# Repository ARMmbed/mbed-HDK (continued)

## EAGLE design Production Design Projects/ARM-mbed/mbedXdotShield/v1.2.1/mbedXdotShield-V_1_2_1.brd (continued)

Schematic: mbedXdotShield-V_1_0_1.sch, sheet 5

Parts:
BRD1: K64F/K22F-SHIELD; K64F/K22F
D1: BAT60A; SOD323
R14, R15, R16, R17, R18, R19, R20, R21, R22, R23, R24, R25, R26: 220R; 0402
R27: 0; 0402
SW3: JS202011JCQN

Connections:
GND: BRD1.6 (GND), BRD1.7 (GND), BRD1.29 (GND); also elsewhere on the board
GPIO2: R15.1; also elsewhere on the board
GPIO3: R16.1; also elsewhere on the board
I2C0_SCL: R26.2; also elsewhere on the board
I2C0_SDA: R25.2; also elsewhere on the board
unnamed: BRD1.9 (A0), R14.2
unnamed: BRD1.10 (A1), R15.2
unnamed: BRD1.11 (A2), R16.2
unnamed: BRD1.15 (D0/RX), R17.1
unnamed: BRD1.16 (D1/TX), R18.1
unnamed: BRD1.17 (D2), R19.1
unnamed: BRD1.5 (5V), D1.K
unnamed: BRD1.18 (D3), R20.1
unnamed: BRD1.25 (D10/SS), R21.1
unnamed: BRD1.26 (D11/MOSI), R22.1
unnamed: BRD1.27 (D12/MISO), R23.1
unnamed: BRD1.28 (D13/SCK), R24.1
unnamed: BRD1.31 (SDA), R25.1
unnamed: BRD1.32 (SCL), R26.1
unnamed: BRD1.2 (IOREF), BRD1.4 (3V3), R27.1
unnamed: R17.2, SW3.6
unnamed: R18.2, SW3.2
P5V-VIN: BRD1.8 (VIN); also elsewhere on the board
P5V_USB: D1.A; also elsewhere on the board
SPI_MISO: R23.2; also elsewhere on the board
SPI_MOSI: R22.2; also elsewhere on the board
SPI_NSS: R21.2; also elsewhere on the board
SPI_SCK: R24.2; also elsewhere on the board
TGT_NRESET: BRD1.3 (NRESET); also elsewhere on the board
UART1_CTS: R19.2; also elsewhere on the board
UART1_RTS: R20.2; also elsewhere on the board
UART1_RX: SW3.3, SW3.5; also elsewhere on the board
UART1_TX: SW3.1, SW3.7; also elsewhere on the board
WAKE: R14.1; also elsewhere on the board

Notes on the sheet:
Board Headers
UART Swap - DPDT Switch

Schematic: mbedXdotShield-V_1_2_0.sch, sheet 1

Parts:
ANT1: M620720
C1: 10uF; 0603
C2: 100nF; 0603
C3: 9.1pF; 0402
C4: 5.6pF; 0402
C5: 10pF; 0402
C6: 82pF; 0402
C7: 6.8pF; 0402
L1: 7.5nH; 0402
R1, R6: 0; 0402
U1: MTXDOT-EU1-A00-1; MTXDOT-EU1/NA1-A00-1

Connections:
ANT1: C3.1, C4.2, L1.1, R1.1, U1.P$37 (ANT1)
GND: C1.2, C2.2, C4.1, C5.1, C6.1, C7.1, U1.P$1 (GND(0)), U1.P$5 (GND(1)), U1.P$17 (GND(2)), U1.P$20 (GND(3)), U1.P$35 (GND(4)), U1.P$36 (GND(5)), U1.P$38 (GND(6)), U1.P$39 (GND(7)), U1.P$40 (GND(8)), U1.P$41 (GND(9)), U1.P$42 (GND(10)), U1.P$43 (GND(11)), U1.P$44 (GND(12)), U1.P$45 (GND(13)), U1.P$46 (GND(14)), U1.P$48 (GND(15)), U1.P$49 (GND(16)), U1.P$50 (GND(17)), U1.P$51 (GND(18)), U1.P$52 (GND(19)), U1.P$53 (GND(20)), U1.P$54 (GND(21)), U1.P$55 (GND(22)), U1.P$56 (GND(23)), U1.P$57 (GND(24)), U1.P$58 (GND(25)); also elsewhere on the board
GPIO0: U1.P$26 (GPIO0); also elsewhere on the board
GPIO1: U1.P$25 (GPIO1); also elsewhere on the board
GPIO2: U1.P$24 (GPIO2); also elsewhere on the board
GPIO3: U1.P$23 (GPIO3); also elsewhere on the board
I2C0_SCL: U1.P$27 (I2C0_SCL); also elsewhere on the board
I2C0_SDA: U1.P$28 (I2C0_SDA); also elsewhere on the board
unnamed: ANT1.P$3 (3), C7.2
unnamed: ANT1.P$1 (1), C3.2, C5.2, C6.2, L1.2, R1.2
RFU1: U1.P$2 (RFU1)
RFU2: R6.2, U1.P$6 (RFU2)
RFU3: U1.P$7 (RFU3)
RFU4: U1.P$8 (RFU4)
RFU5: U1.P$18 (RFU5)
RFU6: U1.P$19 (RFU6)
RFU7: U1.P$21 (RFU7)
RFU8: U1.P$22 (RFU8)
SPI_MISO: U1.P$12 (SPI_MISO); also elsewhere on the board
SPI_MOSI: U1.P$11 (SPI_MOSI); also elsewhere on the board
SPI_NSS: U1.P$9 (SPI_NSS); also elsewhere on the board
SPI_SCK: U1.P$10 (SPI_SCK); also elsewhere on the board
TGT_NRESET: U1.P$33 (NRESET); also elsewhere on the board
TGT_RX: U1.P$16 (UART0_RX); also elsewhere on the board
TGT_SWCLK: U1.P$29 (SWCLK); also elsewhere on the board
TGT_SWDIO: U1.P$30 (SWDIO); also elsewhere on the board
TGT_TX: U1.P$15 (UART0_TX); also elsewhere on the board
UART1_CTS: U1.P$32 (UART1_CTS); also elsewhere on the board
UART1_RTS: U1.P$31 (UART1_RTS); also elsewhere on the board
UART1_RX: U1.P$14 (UART1_RX); also elsewhere on the board
UART1_TX: U1.P$13 (UART1_TX); also elsewhere on the board
WAKE: U1.P$34 (WAKE); also elsewhere on the board

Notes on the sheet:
Target Microcontroller - Multitech xDOT
DNP

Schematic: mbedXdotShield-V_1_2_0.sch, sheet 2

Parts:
C8, C9, C16: 10uF; 0603
CON1: 47346-0001; USB-MICRO-B-H
CON2: S2B-PH-SM4-TB(LF)(SN)
D3, D4, D5: BAT60A; SOD323
R29: 0; 0805
U2: TLV73333PDBVT; SOT23-5

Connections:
GND: C8.2, C9.2, C16.2, CON1.GND, CON2.2 (-), U2.2 (GND); also elsewhere on the board
P5V-VIN: D4.A; also elsewhere on the board
P5V_USB: C16.1, CON1.VBUS, D3.A; also elsewhere on the board
USB_D+: CON1.D+; also elsewhere on the board
USB_D-: CON1.D-; also elsewhere on the board

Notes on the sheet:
3.3V Regulator
Micro USB Connector
4.5V Battery Connector

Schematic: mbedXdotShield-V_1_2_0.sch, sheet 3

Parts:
C10, C11: 100nF; 0402
C12, C13, C14, C15: 18pF; 0402
D6: BAT60J; SOD323
LED3: RED; CHIPLED_0603
LED4: BLUE; CHIPLED_0603
LED5: GREEN; CHIPLED_0603
Q1: 12MHz; 3.2X.2.5
R4, R7: 33R; 0402
R8, R12, R13: 1.5K; 0402
R9, R10: 10K; 0402
R11: 470R; 0402
RESET: SKRKAEE010
T1: BSS84; SOT23-3
U4: IF-LPC11U35; HVQFN33

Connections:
GND: C10.2, C11.2, C12.2, C13.2, C14.2, C15.2, RESET.P$1, U4.EXP (VSS); also elsewhere on the board
HID: R12.2, U4.12 (LED_HID)
IF_NRESET: C10.1, R9.2, U4.2 (IF_NRESET)
ISP: D6.K, RESET.P$2 (S), U4.1 (NRESET_FB_BL), U4.3 (NRESET_FB_ISP)
MSD: R11.2, U4.7 (LED_MSD)
unnamed: C13.1, R4.2, R8.2, U4.14 (USB_D+)
unnamed: C12.1, R7.2, U4.13 (USB_D-)
unnamed: T1.1 (G), U4.15 (USB_SCON)
unnamed: R8.1, T1.3 (D)
unnamed: R10.2, U4.9 (USB_VBUS)
unnamed: LED3.C, R11.1
unnamed: LED4.C, R12.1
unnamed: LED5.C, R13.1
unnamed: C15.1, Q1.P$3 (2), U4.5 (XTALOUT)
unnamed: C14.1, Q1.P$1 (1), U4.4 (XTALIN)
TGT_NRESET: D6.A, U4.8 (TGT_NRESET); also elsewhere on the board
TGT_RX: U4.32 (TGT_RX); also elsewhere on the board
TGT_SWCLK: U4.16 (TGT_SWCLK); also elsewhere on the board
TGT_SWDIO: U4.17 (TGT_SWDIO); also elsewhere on the board
TGT_TX: U4.31 (TGT_TX); also elsewhere on the board
UART: R13.2, U4.21 (LED_UART)
USB_D+: R4.1; also elsewhere on the board
USB_D-: R7.1; also elsewhere on the board

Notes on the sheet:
LCP11u35 DAPLINK Interface

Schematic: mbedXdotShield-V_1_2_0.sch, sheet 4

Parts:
C17: 100nF; 0603
LED1: SMD_LED0603; CHIPLED_0603
LED2: SMD_LED1206; CHIPLED_1206
R2, R5: 1.5K; 0402
R3: 220R; 0402
R28: 0; 0402
SW1: SKRKAEE010
U3: AT45DB321E-SHF-B; SO8

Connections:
GND: C17.1, LED1.C, LED2.C, SW1.P$2 (S), U3.7 (GND); also elsewhere on the board
GPIO0: R3.2; also elsewhere on the board
GPIO1: R5.1, SW1.P$1; also elsewhere on the board
unnamed: LED2.A, R3.1
unnamed: LED1.A, R2.1
unnamed: C17.2, R28.1, U3.6 (VCC)
SPI_MISO: U3.8 (SO); also elsewhere on the board
SPI_MOSI: U3.1 (SI); also elsewhere on the board
SPI_NSS: U3.4 (!CS); also elsewhere on the board
SPI_SCK: U3.2 (SCK); also elsewhere on the board

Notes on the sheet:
SW2
Power LED
User LED
SPI Flash Memory

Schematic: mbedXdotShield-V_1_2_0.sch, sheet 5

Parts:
BRD1: K64F/K22F-SHIELD; K64F/K22F
D1: BAT60A; SOD323
R14, R15, R16, R17, R18, R19, R20, R21, R22, R23, R24, R25, R26: 220R; 0402
R27: 0; 0402
SW3: JS202011JCQN

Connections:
GND: BRD1.6 (GND), BRD1.7 (GND), BRD1.29 (GND); also elsewhere on the board
GPIO2: R15.1; also elsewhere on the board
GPIO3: R16.1; also elsewhere on the board
I2C0_SCL: R26.2; also elsewhere on the board
I2C0_SDA: R25.2; also elsewhere on the board
unnamed: BRD1.9 (A0), R14.2
unnamed: BRD1.10 (A1), R15.2
unnamed: BRD1.11 (A2), R16.2
unnamed: BRD1.15 (D0/RX), R17.1
unnamed: BRD1.16 (D1/TX), R18.1
unnamed: BRD1.17 (D2), R19.1
unnamed: BRD1.5 (5V), D1.K
unnamed: BRD1.18 (D3), R20.1
unnamed: BRD1.25 (D10/SS), R21.1
unnamed: BRD1.26 (D11/MOSI), R22.1
unnamed: BRD1.27 (D12/MISO), R23.1
unnamed: BRD1.28 (D13/SCK), R24.1
unnamed: BRD1.31 (SDA), R25.1
unnamed: BRD1.32 (SCL), R26.1
unnamed: BRD1.2 (IOREF), BRD1.4 (3V3), R27.1
unnamed: R17.2, SW3.6
unnamed: R18.2, SW3.2
P5V-VIN: BRD1.8 (VIN); also elsewhere on the board
P5V_USB: D1.A; also elsewhere on the board
SPI_MISO: R23.2; also elsewhere on the board
SPI_MOSI: R22.2; also elsewhere on the board
SPI_NSS: R21.2; also elsewhere on the board
SPI_SCK: R24.2; also elsewhere on the board
TGT_NRESET: BRD1.3 (NRESET); also elsewhere on the board
UART1_CTS: R19.2; also elsewhere on the board
UART1_RTS: R20.2; also elsewhere on the board
UART1_RX: SW3.3, SW3.5; also elsewhere on the board
UART1_TX: SW3.1, SW3.7; also elsewhere on the board
WAKE: R14.1; also elsewhere on the board

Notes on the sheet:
Board Headers
UART Swap - DPDT Switch

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
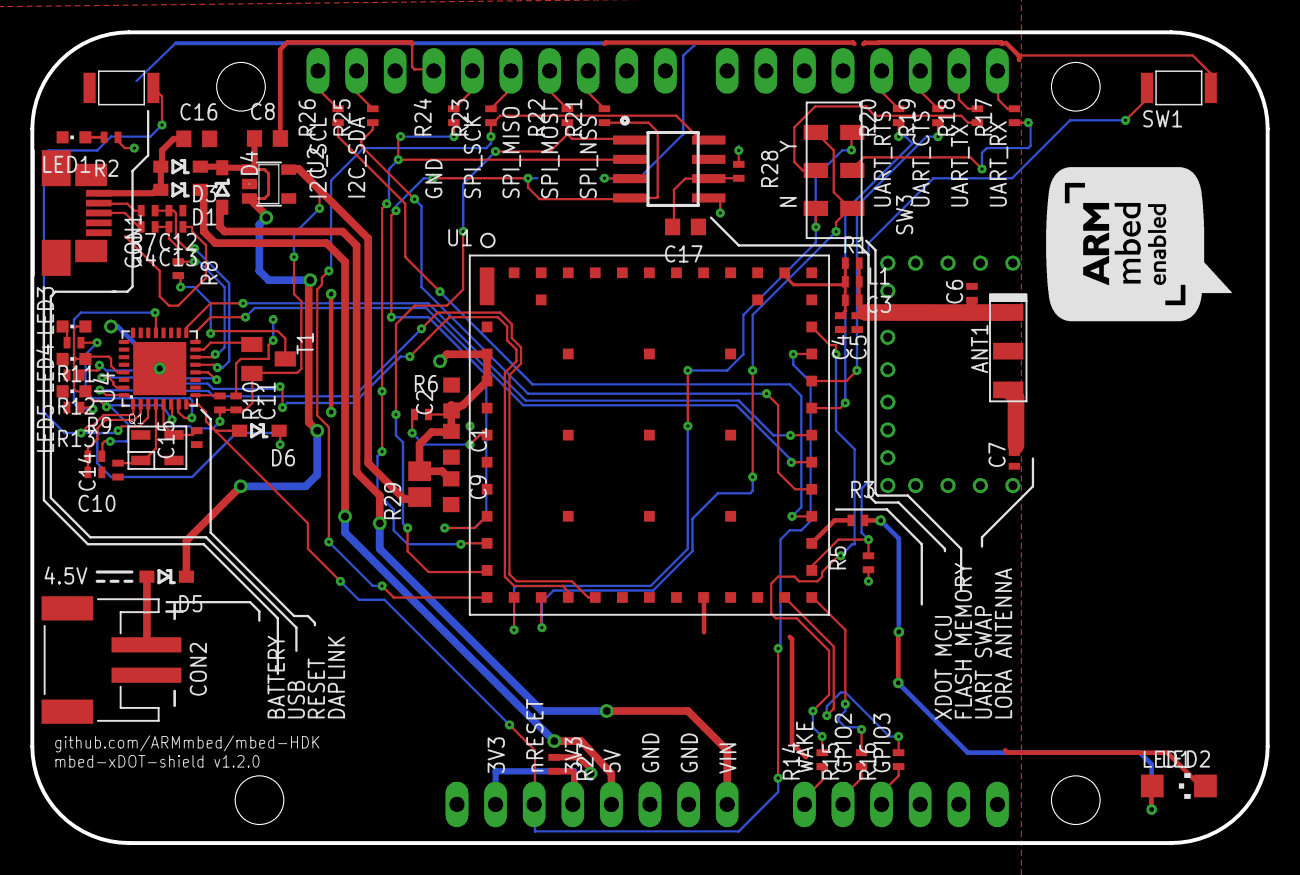
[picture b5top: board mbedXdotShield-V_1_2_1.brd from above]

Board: 2 copper layers, 81.3 x 53.3 mm, 70 parts (0 on the bottom side), 68 nets.

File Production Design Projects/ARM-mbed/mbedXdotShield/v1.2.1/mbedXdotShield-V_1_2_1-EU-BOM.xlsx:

Qty | Value | Device | Package | Parts | Description | MF | MFN | OC-DIGIKEY | OC-MOUSER | OC-NEWARK
1 |  | IF-LPC11U35 | HVQFN33 | U4 | MCU | NXP | LPC11U35FHI33/501, | 568-9586-ND | 771-LPC11U35FHI33501 | 24W5342
3 | 0 | RESISTOR0402 | 402 | R6, R27, R28 | Resistor | Yageo | RC0402JR-070RL | 311-0.0JRCT-ND | 603-RC0402JR-070RL | 603-RC0402JR-070RL
5 | 1.5K | RESISTOR0402 | 402 | R2, R5, R8, R12, R13 | Resistor | Panasonic | ERJ-2RKF1501X | P1.50KLCT-ND | 667-ERJ-2RKF1501X | 2302656
2 | 100nF | CAPACITOR0402 | 402 | C10, C11 | Capacitor | AVX | 0402YD104KAT2A | 478-1126-1-ND | 581-0402YD104K | 1327666
2 | 100nF | CAPACITOR0603 | 603 | C2, C17 | Capacitor | AVX | 0603YC104KAT2A | 478-1239-1-ND | 581-060316C104K | 1327679
2 | 10K | RESISTOR0402 | 402 | R9, R10 | Resistor | Vishay | CRCW040210K0JNED | 541-10KJCT-ND | 71-CRCW0402J-10K-E3 | 59M6696
4 | 10uF | CAPACITOR0603 | 603 | C1, C8, C9, C16 | Capacitor | Yageo | CC0603MRX5R5BB106 | 311-1448-1-ND | 603-CC603MRX5R5BB106 | 1458902
1 | 12MHz | Q_3.2X2.5 | 3.2X.2.5 | Q1 | XTAL | TXC | 7M-12.000MAAJ-T | 887-1121-1-ND | 717-7M-12.000MAAJ-T | 84R5706
4 | 18pF | CAPACITOR0402 | 402 | C12, C13, C14, C15 | Capacitor | Murata | GRM1555C1H180JA01D | 490-5858-6-ND |  | 14T3293
14 | 220R | RESISTOR0402 | 402 | R3, R14, R15, R16, R17, R18, R19, R20, R21, R22, R23, R24, R25, R26 | Resistor | Vishay | CRCW0402220RJNED | 541-220JCT-ND | 71-CRCW0402J-220-E3 | 1514687
2 | 33R | RESISTOR0402 | 402 | R4, R7 | Resistor | Vishay | CRCW040233R0JNED | 541-33JCT-ND | 71-CRCW0402J-33-E3 | 72M6782
1 | 470R | RESISTOR0402 | 402 | R11 | Resistor | Vishay | CRCW0402470RJNED | 541-470JCT-ND | 71-CRCW0402J-470-E3 | 59M6737
1 | 47346-0001 | 47346-0001 | USB-MICRO-B-H | CON1 | USB Receptacle Horizontal Micro Type B | MOLEX | 47346-0001 |  | 538-47346-0001 | 1568026
1 | 5.6pF | CAPACITOR0402 | 402 | C4 | Capacitor | AVX | 04025U5R6BAT2A | 478-10162-1-ND | 581-04025U5R6BAT2A | 1327642RL
1 | 6.8pF | CAPACITOR0402 | 402 | C7 | Capacitor | Murata | GRM1555C1H6R8BA01D | 490-6252-1-ND | 81-GRM1555C1H6R8BA1D | 2611902
1 | 82pF | CAPACITOR0402 | 402 | C6 | Capacitor | Murata | GRM1555C1H820JA01D | 490-5879-1-ND | 81-GRM1555C1H820JA1D | 2470460
1 | 9.1pF | CAPACITOR0402 | 402 | C3 | Capacitor | Murata | GJM1555C1H9R1CB01D | 490-3112-1-ND | 81-GJM1555C1H9R1CB01 | 41M1583
1 | 0 | RESISTOR0805 | 805 | R29 | Resistor | Yageo | RC0805JR-070RL | 311-0.0ARCT-ND | 603-RC0805JR-070RL | 1799478
1 | AT45DB321E-SHF-B | AT45DB321E-SHF-B | SO8 | U3 | Serial Flash 32 Mb 85 Mhz | Adesto Technologies | AT45DB321E-SHF-B | 1265-1072-5-ND | 988-AT45DB321E-SHF-B | 2414318
4 | BAT60A | BAT60A | SOD323 | D1, D3, D4, D5 | SCHOTTKY DIODE | Infineon | BAT60AE6327HTSA1 | BAT60AE6327HTSA1CT-ND | 726-BAT60AE6327 | 85X4127
1 | BAT60J | BAT60J | SOD323 | D6 | SCHOTTKY DIODE | STMicroelectronics | BAT60JFILM | 497-3707-6-ND | 511-BAT60JFILM | 89K1218
1 | BLUE | SMD_LED0603 | CHIPLED_0603 | LED4 | LED SMD, Colour Blue | Wurth Electronics Inc | 150060BS75000 | 732-4966-1-ND | 710-150060BS75000 | 2322069
1 | BSS84 | BSS84 | SOT23-3 | T1 | MOSFET P-CHANNEL | Fairchild Semiconductor | BSS84 | BSS84CT-ND | 512-BSS84 | 58K8770
1 | GREEN | SMD_LED0603 | CHIPLED_0603 | LED5 | LED SMD, Colour Green | Wurth Electronics Inc | 150060GS75000 | 732-4971-1-ND | 710-150060GS75000 | 2322070
1 | K64F/K22F-SHIELD | K64F/K22F-SHIELD | K64F/K22F | BRD1 | Shield for K64F/K22F | SparkFun | 1568-1413-ND
1 | M620720 | M620720 | M620720 | ANT1 | Chip Antenna Ceramic ISM/M2M/IoT 868/915MHz | Ethertronics | M620720 | 939-1066-1-ND
1 | MTXDOT-EU1-A00-1 | MTXDOT-EU1-A00-1 | MTXDOT-EU1/NA1-A00-1 | U1 | Multitech xDOT LORA MODULE UFL/TRC 868MHz for Europe | Multi-Tech Systems Inc. | MTXDOT-EU1-A00-1 | 591-1292-ND
2 | RED | SMD_LED0603 | CHIPLED_0603 | LED1, LED3 | LED SMD, Colour Red | Wurth Electronics Inc | 150060RS75000 | 732-4978-1-ND | 710-150060RS75000 | 2322071
1 | S2B-PH-SM4-TB(LF)(SN) | S2B-PH-SM4-TB(LF)(SN) | S2B-PH-SM4-TB(LF)(SN) | CON2 | 2 Position 2 mm JST PH Series Pitch Surface Mount Side Entry Shrouded Header | JST | S2B-PH-SM4-TB(LF)(SN) | 455-1749-1-ND |  | 38K8067
2 | SKRKAEE010 | SKRKAEE010 | SKRKAEE010 | RESET, SW2 | MOMENTARY SWITCH PUSH VERTICAL (SPST) | ALPS | SKRKAEE010 |  | 688-SKRKAE
1 | SMD_LED1206 | SMD_LED1206 | CHIPLED_1206 | LED2 | LED SMD, Colour Blue | Wurth Electronics Inc | 150120BS75000 | 732-4989-1-ND | 710-150120BS75000 | 2322084
1 | TLV73333PDBVT | TLV73333PDBVT | SOT23-5 | U2 | LDO Fixed Regulator 3.3v, 300mA | Texas Instruments | TLV73333PDBVT | 296-38492-1-ND | 595-TLV73333PDBVT | 2455145
1 | JS202011JCQN | JS202011JCQN | JS202011JCQN | SW3 | SLIDE TOGGLE SWITCH VERTICAL (DPDT) | C&K Components | JS202011JCQN | CKN10723CT-ND | 611-JS202011JCQN

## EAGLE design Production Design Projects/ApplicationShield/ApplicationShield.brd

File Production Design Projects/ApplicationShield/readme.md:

## Application Shield

The Application Shield includes an array of connectivity, sensors and display options to enable the maximum number of potential experiments with Arduino form factor mbed development boards.

## Whats included here?

* Eagle Schematic and Board files
* PDF Schematic and Board copies
* CAM Job GERBERS for manufacture (including pick/place and drill)
* BOM (Bill of Materials) In .csv or eBOM

## Hardware

The hardware design files can be found in this repo as part of the mbed HDK. The design features:

        1. 128x32 Graphics LCD
        2. 5 way joystick
        3. 2 x Potentiometers
        4. Speaker, PWM Conencted
        5. 3 Axis +/1 1.5g Accelerometer
        6. RGB LED, PWM connected
        7. Temperature sensor
        8. Socket for for Xbee (Zigbee) or RN-XV (Wifi)

## Software and more info

The software and more info can be found in the [mbed component page](https://developer.mbed.org/components/mbed-Application-Shield/). 

## How to get hardware

1. Buy pre-assembled board from   
  * [Cool Components](http://www.coolcomponents.co.uk/mbed-application-shield.html)
  * [Switch Science](http://international.switch-science.com/catalog/1810/)
  * [Farnell](http://uk.farnell.com/keil/mbed-016-1/application-shield-arduino-dev/dp/2468119)
2. Do it yourself, using supplied GERBERS and BOM/eBOM with fabrication house.

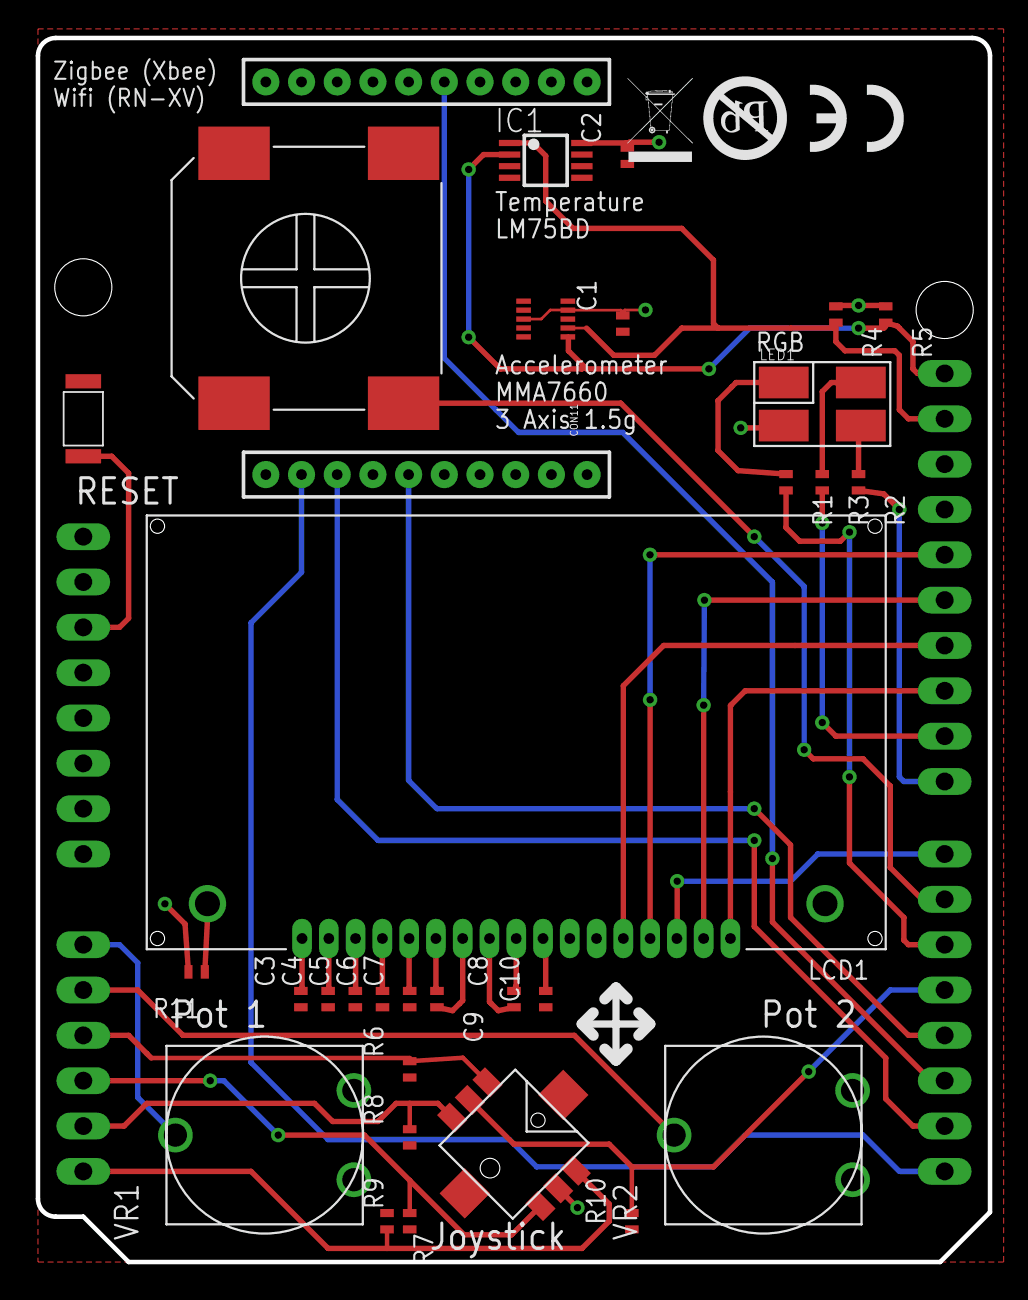
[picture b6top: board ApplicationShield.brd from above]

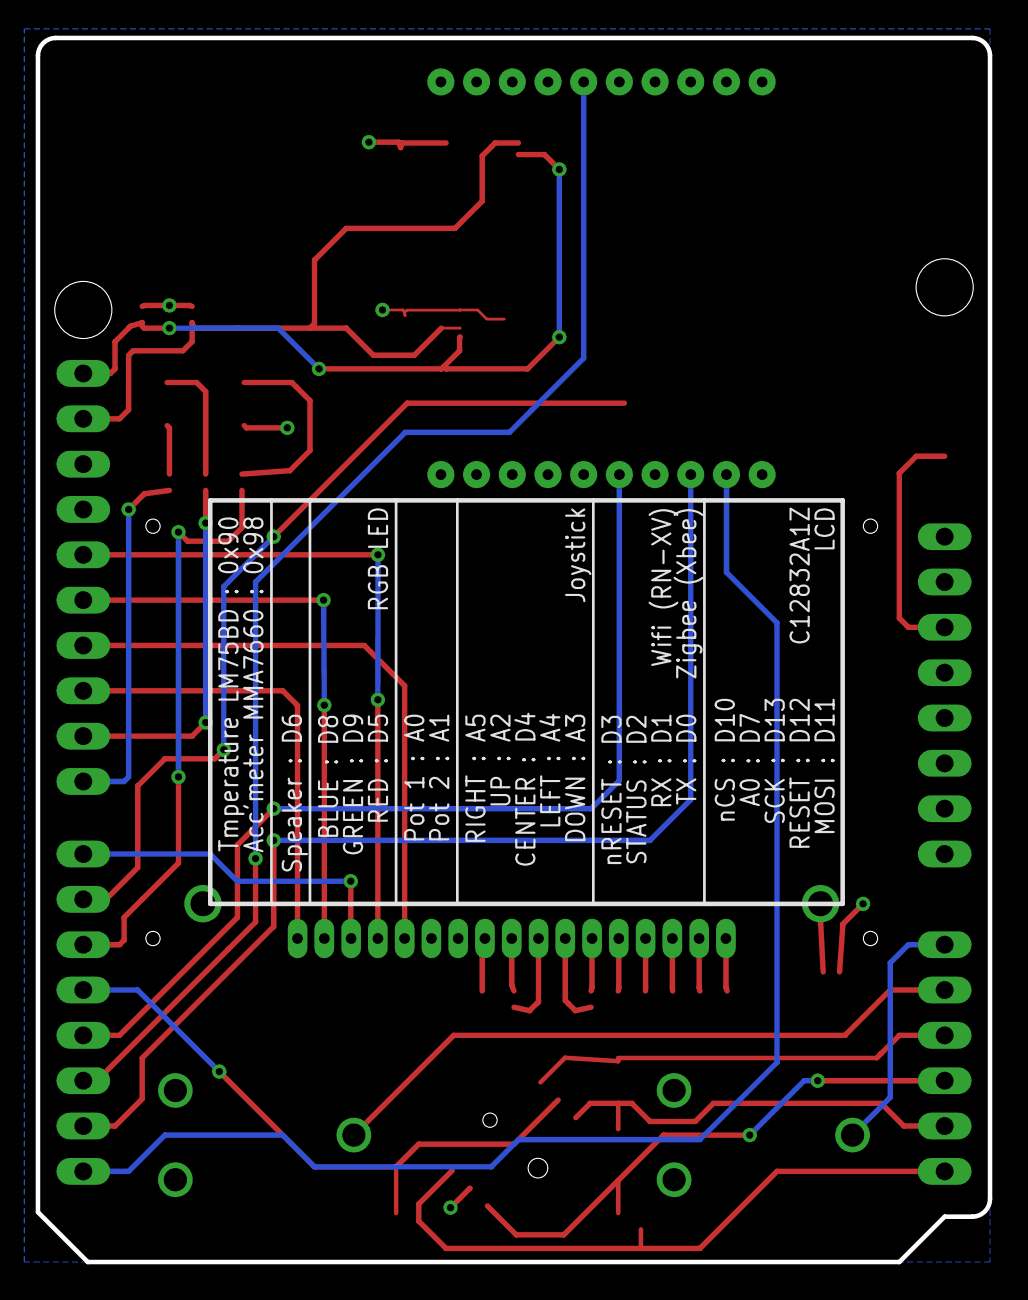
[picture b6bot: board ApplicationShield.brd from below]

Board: 2 copper layers, 53.3 x 68.6 mm, 35 parts (3 on the bottom side), 39 nets.

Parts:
BRD1: ARDUINO_R3_APPS; ARDUINO_R3_APPS_SHEILD
C1, C2, C3, C4, C5, C6, C7, C8, C9, C10: 100nF; 0402
CON11: XBEE-1B2; XBEE-SILK
IC1: LM75BD_TSSOP8; TSSOP8
IC2: MMA7660FC; DFN10-3X3MM
LCD1: C12832A1Z
LED1: CLV1A-FKB; PLCC-4
R1, R2, R3: 1k; 0402
R4, R5, R6, R7, R8, R9, R10: 4k7; 0402
R11: 220R; 0402
SPK1: SMS-1508MS; SMS-1508MS-R
SS1: PB-MARK; PB-MARK-0.2
SS2: CE-MARK; CE-MARK-0.2
SS3: WEEE-MARK; WEEE-MARK-0.2
SW1: SPST_SKRKAWW010; SKRKAEE010
SW2: ALPS_NAVSWITCH; SKRHA_SERIES
VR1, VR2: ISKRA_PNZ; CA14V

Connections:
+3.3V: BRD1.P$4, C1.1, C2.1, CON11.1, IC1.8, IC2.P$3, IC2.P$9, LCD1.P$12, LED1.2, R4.2, R5.2, R11.1, SW2.P$5, VR1.P$3, VR2.P$3
GND: BRD1.P$6, BRD1.P$7, C1.2, C2.2, C3.2, C4.2, C5.2, C6.2, C7.2, C10.2, CON11.10, IC1.4, IC1.5, IC1.6, IC1.7, IC2.P$4, IC2.P$8, LCD1.K, LCD1.P$11, R6.2, R7.2, R8.2, R9.2, R10.2, SPK1.-, SW1.P$1, VR1.P$1, VR2.P$1
LCD_A0: BRD1.P$22, LCD1.P$15
LCD_CS_N: BRD1.P$25, LCD1.P$17
LCD_MOSI: BRD1.P$26, LCD1.P$13
LCD_RESET: BRD1.P$27, LCD1.P$16
LCD_SCK: BRD1.P$28, LCD1.P$14
LED_BLUE: BRD1.P$23, R2.1
LED_GREEN: BRD1.P$24, R3.1
LED_RED: BRD1.P$20, R1.1
unnamed: LCD1.A, R11.2
unnamed: C8.1, LCD1.P$9
unnamed: C8.2, LCD1.P$8
unnamed: C9.1, LCD1.P$7
unnamed: C9.2, LCD1.P$6
unnamed: C3.1, LCD1.P$1
unnamed: C4.1, LCD1.P$2
unnamed: C5.1, LCD1.P$3
unnamed: C6.1, LCD1.P$4
unnamed: C7.1, LCD1.P$5
unnamed: LED1.1, R1.2
unnamed: C10.1, LCD1.P$10
unnamed: LED1.4, R3.2
unnamed: LED1.3, R2.2
NRESET: BRD1.P$3, SW1.P$2
POT_1: BRD1.P$9, VR1.P$2
POT_2: BRD1.P$10, VR2.P$2
SCL: BRD1.P$32, IC1.2, IC2.P$6, R5.1
SDA: BRD1.P$31, IC1.1, IC2.P$7, R4.1
SPEAKER: BRD1.P$21, SPK1.+
SW_CENTER: BRD1.P$19, R10.1, SW2.P$2
SW_DOWN: BRD1.P$12, R9.1, SW2.P$4
SW_LEFT: BRD1.P$13, R8.1, SW2.P$1
SW_RIGHT: BRD1.P$14, R7.1, SW2.P$6
SW_UP: BRD1.P$11, R6.1, SW2.P$3
XBEE_NRST: BRD1.P$18, CON11.5
XBEE_RX: BRD1.P$16, CON11.3
XBEE_STATUS: BRD1.P$17, CON11.15
XBEE_TX: BRD1.P$15, CON11.2
